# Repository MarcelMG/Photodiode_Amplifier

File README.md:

# Photodiode_Amplifier
digitally selectable variable gain transimpedance amplifier for photodiodes

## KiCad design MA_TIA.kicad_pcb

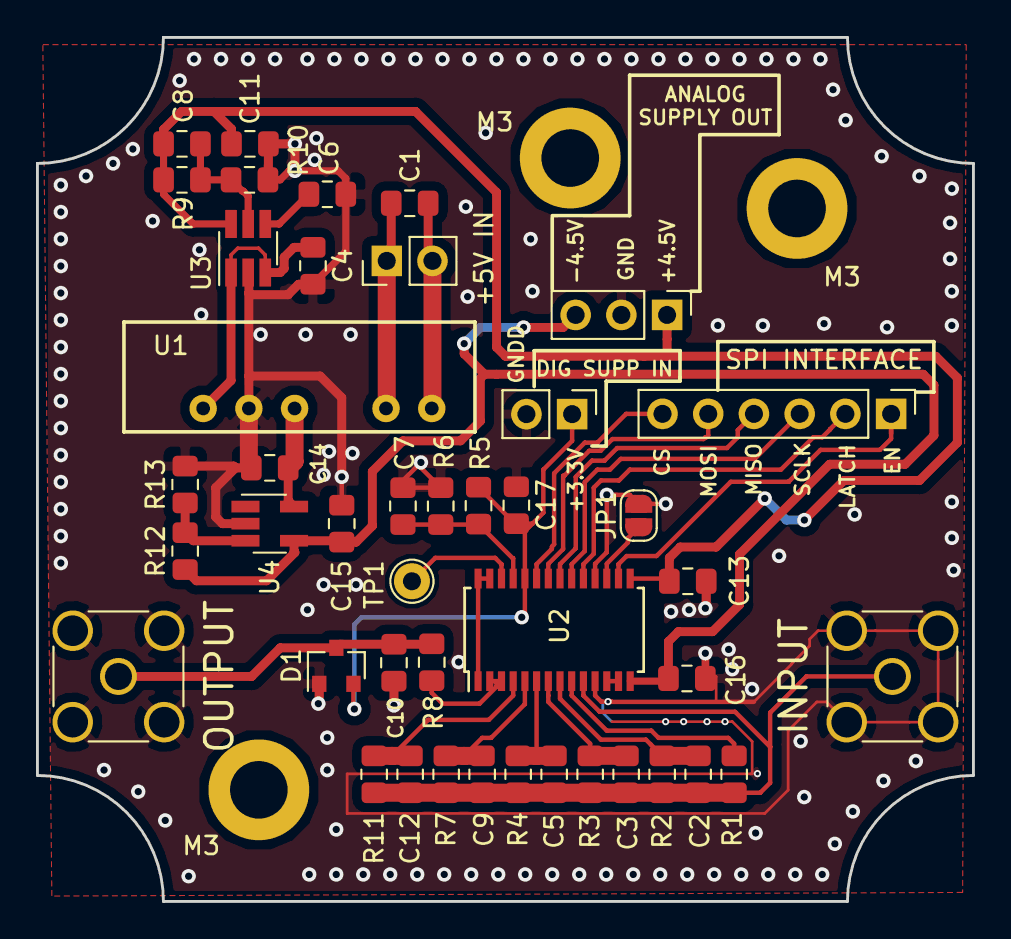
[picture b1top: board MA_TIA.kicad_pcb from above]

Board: 2 copper layers, 52.0 x 48.0 mm, 46 parts (0 on the bottom side), 31 nets.

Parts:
+4.5V: analog_supply; PinHeader_1x03_P2.54mm_Vertical
+5V IN: pwr_input_5V; PinHeader_1x02_P2.54mm_Vertical
C1: 2.2µ; C_0805_2012Metric_Pad1.15x1.40mm_HandSolder
C2: 6.2p; C_0805_2012Metric_Pad1.15x1.40mm_HandSolder
C3: 62p; C_0805_2012Metric_Pad1.15x1.40mm_HandSolder
C4, C14: 1µ; C_0805_2012Metric_Pad1.15x1.40mm_HandSolder
C5: 620p; C_0805_2012Metric_Pad1.15x1.40mm_HandSolder
C6: 10n; C_0805_2012Metric_Pad1.15x1.40mm_HandSolder
C7, C13, C16, C17: 100n; C_0805_2012Metric_Pad1.15x1.40mm_HandSolder
C8: 68p; C_0805_2012Metric_Pad1.15x1.40mm_HandSolder
C9: 6.2n; C_0805_2012Metric_Pad1.15x1.40mm_HandSolder
C10: 120n; C_0805_2012Metric_Pad1.15x1.40mm_HandSolder
C11, C15: 4.7µ; C_0805_2012Metric_Pad1.15x1.40mm_HandSolder
C12: 62n; C_0805_2012Metric_Pad1.15x1.40mm_HandSolder
D1: BAT54S; SOT-23
DIG SUPP IN: digital_pwr; PinHeader_1x02_P2.54mm_Vertical
INPUT: Photodiode_conn; SMA_TE_5-1814400-1
JP1: SolderJumper-2_P1.3mm_Open_RoundedPad1.0x1.5mm
M3, M3#2, M3#3: MountingHole_3.2mm_M3_DIN965_Pad
OUTPUT: Signal_Out; SMA_TE_5-1814400-1
R1: 10M; R_0805_2012Metric_Pad1.15x1.40mm_HandSolder
R2: 1M; R_0805_2012Metric_Pad1.15x1.40mm_HandSolder
R3: 100k; R_0805_2012Metric_Pad1.15x1.40mm_HandSolder
R4, R5, R6: 10k; R_0805_2012Metric_Pad1.15x1.40mm_HandSolder
R7: 1k; R_0805_2012Metric_Pad1.15x1.40mm_HandSolder
R8: 50; R_0805_2012Metric_Pad1.15x1.40mm_HandSolder
R9: 15k; R_0805_2012Metric_Pad1.15x1.40mm_HandSolder
R10: 5.6k; R_0805_2012Metric_Pad1.15x1.40mm_HandSolder
R11: 100; R_0805_2012Metric_Pad1.15x1.40mm_HandSolder
R12: 33k; R_0805_2012Metric_Pad1.15x1.40mm_HandSolder
R13: 12k; R_0805_2012Metric_Pad1.15x1.40mm_HandSolder
SPI INTERFACE: digital_interface; PinHeader_1x06_P2.54mm_Vertical
TP1: TestPoint; TestPoint_THTPad_D2.0mm_Drill1.0mm
U1: TMA0505D
U2: ADA4350; TSSOP-28_4.4x9.7mm_P0.65mm
U3: TPS79301-EP; SOT-23-6_Handsoldering
U4: MIC5270; SOT-23-5_HandSoldering

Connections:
+3V3: C17.2, D1.2, DIG SUPP IN.1, R5.2, U2.24
+5V: C4.1, U1.5, U3.1, U3.3
-5V: C14.1, U1.3, U4.5
CS: SPI INTERFACE.6, U2.23
EN: SPI INTERFACE.1, U2.16
GND: +4.5V.2, C4.2, C6.2, C7.1, C10.1, C11.2, C13.2, C14.2, C15.2, C16.2, C17.1, D1.1, DIG SUPP IN.2, INPUT.2, JP1.2, OUTPUT.2, R6.1, R10.2, R13.2, U1.4, U2.11, U2.18, U3.2, U4.2
LATCH: SPI INTERFACE.2, U2.19
MISO: SPI INTERFACE.4, U2.21
MOSI: SPI INTERFACE.5, U2.22
unnamed: +5V IN.2, C1.1, U1.1
unnamed: +5V IN.1, C1.2, U1.2
unnamed: C2.2, R2.1, U2.8
unnamed: C3.2, R3.1, U2.7
unnamed: C5.2, R4.1, U2.6
unnamed: C6.1, U3.4
unnamed: C7.2, R5.1, R6.2, U2.25
unnamed: C8.2, R9.2, R10.1, U3.5
unnamed: C9.2, R7.1, U2.5
unnamed: C10.2, D1.3, OUTPUT.1, R8.2
unnamed: C2.1, C3.1, C5.1, C9.1, C12.1, INPUT.1, R1.2, R2.2, R3.2, R4.2, R7.2, R11.2, U2.10
unnamed: C12.2, R11.1, U2.4
unnamed: JP1.1, U2.17
unnamed: R1.1, U2.9
unnamed: R8.1, U2.2, U2.3
unnamed: R12.2, R13.1, U4.3
unnamed: TP1.1, U2.26
unnamed: U2.1, U2.27, U2.28
unnamed: U2.12, U2.13
SCLK: SPI INTERFACE.3, U2.20
VDDA: +4.5V.1, C8.1, C11.1, C13.1, R9.1, U2.15, U3.6
VSSA: +4.5V.3, C15.1, C16.1, R12.1, U2.14, U4.4

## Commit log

2019-11-06 moved two mountig holes slightly inwards
2020-01-12 fix: removed separate digital ground
    fix: removed separate digital ground (GNDD) and connected it to GND
2020-01-27 reorganized directory structure
2020-01-27 added images
2020-01-27 added simulation directory & files
